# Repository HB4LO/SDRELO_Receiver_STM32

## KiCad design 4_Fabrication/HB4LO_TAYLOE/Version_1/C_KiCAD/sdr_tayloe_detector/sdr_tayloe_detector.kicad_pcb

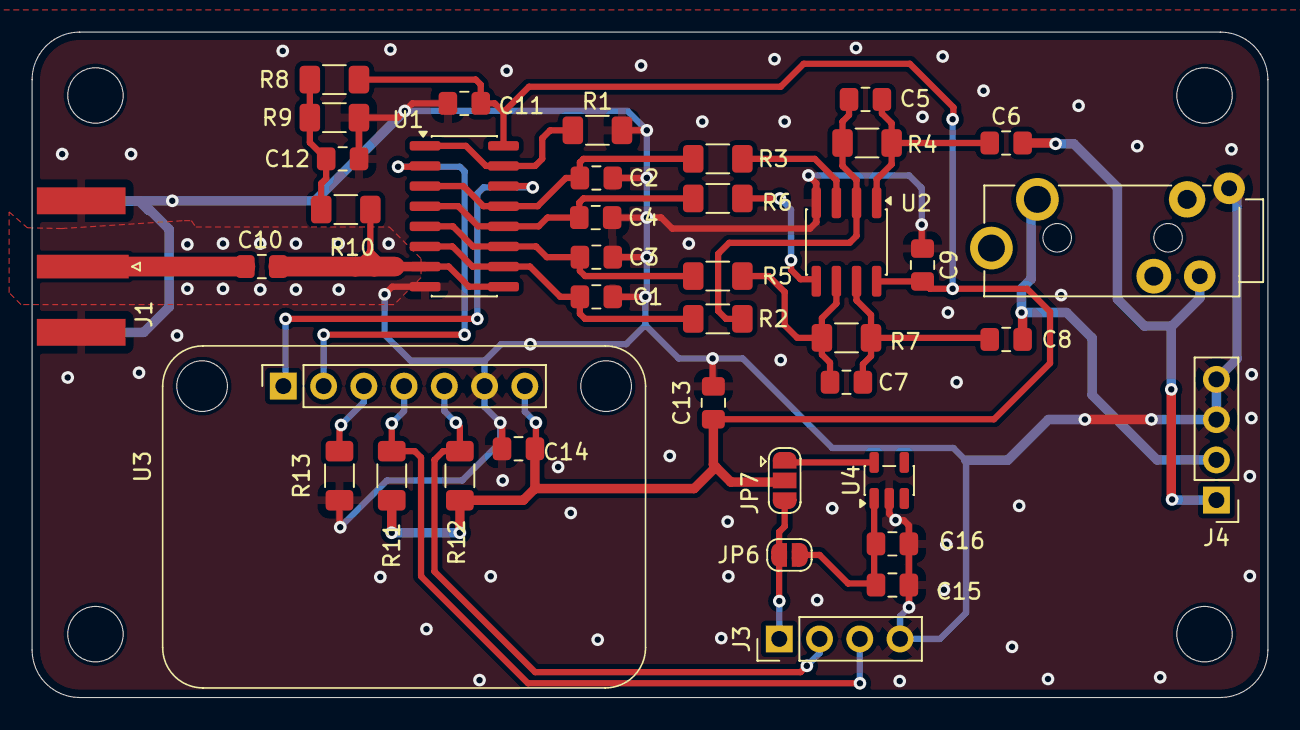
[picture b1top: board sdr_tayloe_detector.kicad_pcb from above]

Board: 2 copper layers, 78.0 x 42.0 mm, 43 parts (0 on the bottom side), 26 nets.

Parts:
C1, C2, C3, C4, C10: 47n; C_0805_2012Metric_Pad1.18x1.45mm_HandSolder
C5, C7: 150p; C_0805_2012Metric_Pad1.18x1.45mm_HandSolder
C6, C8: 2u2; C_0805_2012Metric_Pad1.18x1.45mm_HandSolder
C9, C11, C12, C16: 100n; C_0805_2012Metric_Pad1.18x1.45mm_HandSolder
C13, C14, C15: 1u; C_0805_2012Metric_Pad1.18x1.45mm_HandSolder
H1, H2, H3, H4: M3; MountingHole_3.5mm
J1: Conn_Coaxial; WE_SMA_EndLaunch_PCB1.6
J2: AudioJack4_SwitchTR1_MC001294; Jack_3.5mm_CUI_MC001295
J3, J4: PH4p; PinHeader_1x04_P2.54mm_Vertical
JP6: VCC5V; SolderJumper-2_P1.3mm_Open_RoundedPad1.0x1.5mm
JP7: VCC3V; SolderJumper-3_P1.3mm_Open_RoundedPad1.0x1.5mm
R1, R10, R11, R12: 1K; R_1206_3216Metric_Pad1.30x1.75mm_HandSolder
R2, R3, R5, R6: 100; R_1206_3216Metric_Pad1.30x1.75mm_HandSolder
R4, R7: 68K; R_1206_3216Metric_Pad1.30x1.75mm_HandSolder
R8, R9: 10K; R_1206_3216Metric_Pad1.30x1.75mm_HandSolder
R13: 47; R_1206_3216Metric_Pad1.30x1.75mm_HandSolder
U1: SN74CBT3253; SOIC-16_3.9x9.9mm_P1.27mm
U2: OPA2607; SOIC-8_3.9x4.9mm_P1.27mm
U3: SI5351; SI5351_MODULE
U4: MIC5504-3.3YM5; SOT-23-5

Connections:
+3.3VA: JP7.1 (A), U4.5 (VOUT)
+3V3: C9.2, C11.2, C13.1, C14.1, JP7.2 (C), R8.2, R11.1, R12.1, U1.16 (VCC), U2.8 (V+), U3.7 (VIN)
GND: C1.2, C2.2, C3.2, C4.2, C9.1, C11.1, C12.2, C13.2, C14.2, C15.2, C16.2, J1.2 (Ext), J2.8, J3.4, J4.3, J4.4, R1.2, R9.1, R13.2, U1.8 (GND), U2.4 (V-), U3.6 (GND), U4.2 (GND)
I2C_SCL: J3.3, R11.2, U3.4 (SCL)
I2C_SDA: J3.2, R12.2, U3.5 (SDA)
unnamed: C5.2, C6.1, R4.2, U2.1
unnamed: C7.2, C8.1, R7.2, U2.7
unnamed: C12.1, R8.1, R9.2, R10.1
unnamed: C10.1, J1.1 (In)
unnamed: C6.2, J2.4, J4.1
unnamed: C8.2, J2.6, J4.2
unnamed: C15.1, C16.1, JP6.2 (B), U4.1 (VIN), U4.3 (EN)
unnamed: C10.2, R10.2, U1.7 (1A), U1.9 (2A)
unnamed: C1.1, R2.1, U1.6 (1B1), U1.10 (2B1)
unnamed: C3.1, R5.1, U1.5 (1B2), U1.11 (2B2)
unnamed: C4.1, R6.1, U1.4 (1B3), U1.12 (2B3)
unnamed: C2.1, R3.1, U1.3 (1B4), U1.13 (2B4)
unnamed: R1.1, U1.1 (1~OE), U1.15 (2~OE)
unnamed: U1.14 (S0), U3.1 (CH0)
unnamed: U1.2 (S1), U3.2 (CH1)
unnamed: R3.2, U2.3 (+)
unnamed: C5.1, R2.2, R4.1, U2.2 (-)
unnamed: R6.2, U2.5 (+)
unnamed: C7.1, R5.2, R7.1, U2.6 (-)
unnamed: R13.1, U3.3 (CH2)
VCC: J3.1, JP6.1 (A), JP7.3 (B)

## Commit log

2026-04-16 Initial Public Push
2026-04-21 AudioCard + CAT Control OK
